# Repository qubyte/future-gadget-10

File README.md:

# FG-10

Design files for the FG-10 custom mechanical keyboard.

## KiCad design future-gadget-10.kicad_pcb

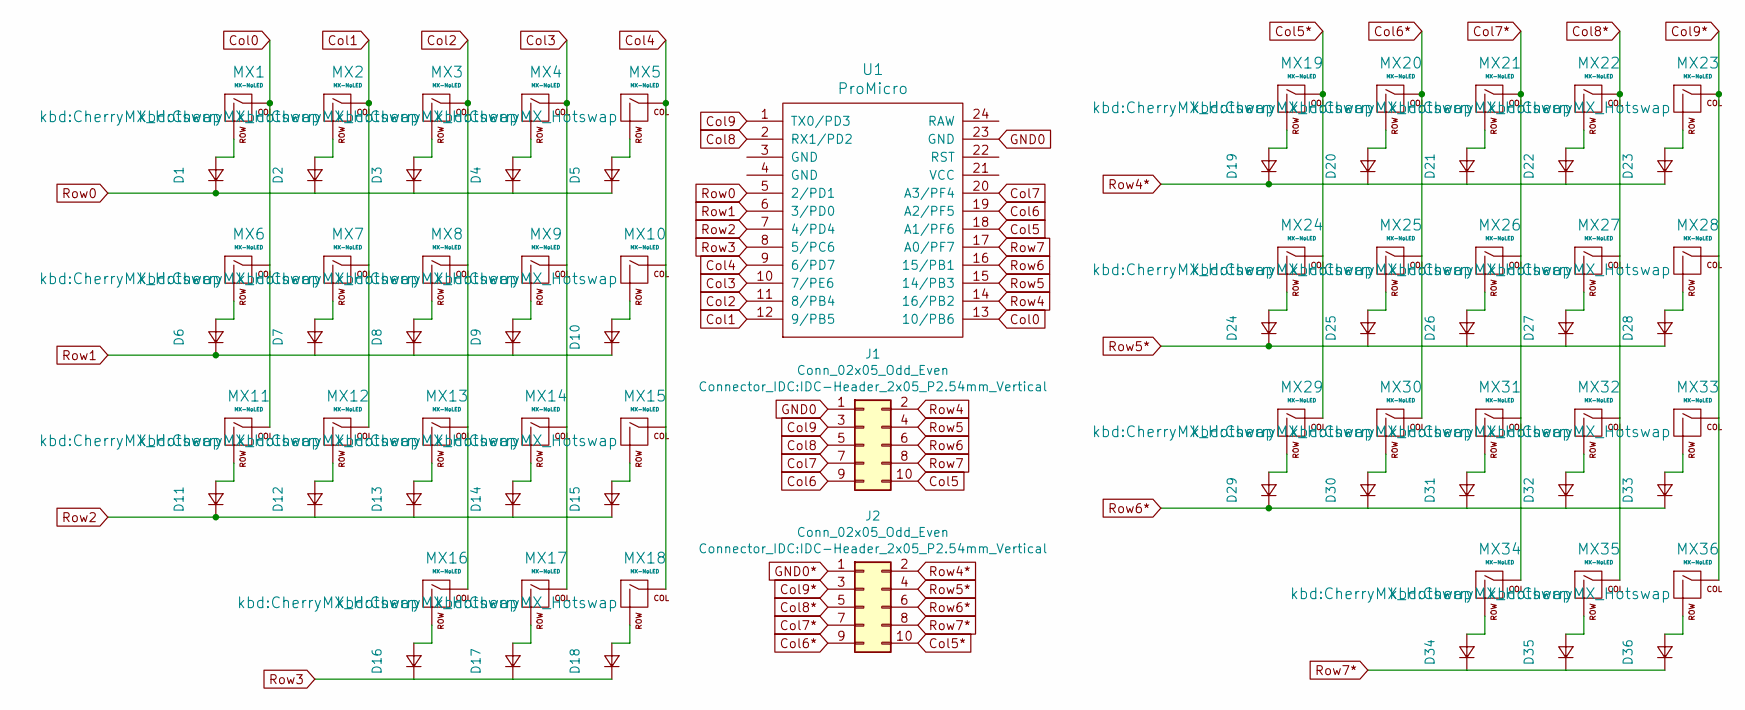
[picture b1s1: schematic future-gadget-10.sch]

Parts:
D1, D2, D3, D4, D5, D6, D7, D8, D9, D10, D11, D12, D13, D14, D15, D16, D17, D18, D19, D20, D21, D22, D23, D24, D25, D26, D27, D28, D29, D30, D31, D32, D33, D34, D35, D36: D_Small; D_SOD-123
J1, J2: Conn_02x05_Odd_Even; IDC-Header_2x05_P2.54mm_Vertical
MX1, MX2, MX3, MX4, MX5, MX6, MX7, MX8, MX9, MX10, MX11, MX12, MX13, MX14, MX15, MX16, MX17, MX18, MX19, MX20, MX21, MX22, MX23, MX24, MX25, MX26, MX27, MX28, MX29, MX30, MX31, MX32, MX33, MX34, MX35, MX36: MX-NoLED; CherryMX_Hotswap
U1: ProMicro; Elite-C

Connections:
Col0: MX1.1 (COL), MX6.1 (COL), MX11.1 (COL), U1.13 (10/PB6)
Col1: MX2.1 (COL), MX7.1 (COL), MX12.1 (COL), U1.12 (9/PB5)
Col2: MX3.1 (COL), MX8.1 (COL), MX13.1 (COL), MX16.1 (COL), U1.11 (8/PB4)
Col3: MX4.1 (COL), MX9.1 (COL), MX14.1 (COL), MX17.1 (COL), U1.10 (7/PE6)
Col4: MX5.1 (COL), MX10.1 (COL), MX15.1 (COL), MX18.1 (COL), U1.9 (6/PD7)
Col5: J1.10, U1.18 (A1/PF6)
Col5*: J2.10, MX19.1 (COL), MX24.1 (COL), MX29.1 (COL)
Col6: J1.9, U1.19 (A2/PF5)
Col6*: J2.9, MX20.1 (COL), MX25.1 (COL), MX30.1 (COL)
Col7: J1.7, U1.20 (A3/PF4)
Col7*: J2.7, MX21.1 (COL), MX26.1 (COL), MX31.1 (COL), MX34.1 (COL)
Col8: J1.5, U1.2 (RX1/PD2)
Col8*: J2.5, MX22.1 (COL), MX27.1 (COL), MX32.1 (COL), MX35.1 (COL)
Col9: J1.3, U1.1 (TX0/PD3)
Col9*: J2.3, MX23.1 (COL), MX28.1 (COL), MX33.1 (COL), MX36.1 (COL)
GND0: J1.1, U1.23 (GND)
GND0*: J2.1
unnamed: D1.2 (A), MX1.2 (ROW)
unnamed: D2.2 (A), MX2.2 (ROW)
unnamed: D3.2 (A), MX3.2 (ROW)
unnamed: D4.2 (A), MX4.2 (ROW)
unnamed: D5.2 (A), MX5.2 (ROW)
unnamed: D6.2 (A), MX6.2 (ROW)
unnamed: D7.2 (A), MX7.2 (ROW)
unnamed: D8.2 (A), MX8.2 (ROW)
unnamed: D9.2 (A), MX9.2 (ROW)
unnamed: D10.2 (A), MX10.2 (ROW)
unnamed: D11.2 (A), MX11.2 (ROW)
unnamed: D12.2 (A), MX12.2 (ROW)
unnamed: D13.2 (A), MX13.2 (ROW)
unnamed: D14.2 (A), MX14.2 (ROW)
unnamed: D15.2 (A), MX15.2 (ROW)
unnamed: D16.2 (A), MX16.2 (ROW)
unnamed: D17.2 (A), MX17.2 (ROW)
unnamed: D18.2 (A), MX18.2 (ROW)
unnamed: D19.2 (A), MX19.2 (ROW)
unnamed: D20.2 (A), MX20.2 (ROW)
unnamed: D21.2 (A), MX21.2 (ROW)
unnamed: D22.2 (A), MX22.2 (ROW)
unnamed: D23.2 (A), MX23.2 (ROW)
unnamed: D24.2 (A), MX24.2 (ROW)
unnamed: D25.2 (A), MX25.2 (ROW)
unnamed: D26.2 (A), MX26.2 (ROW)
unnamed: D27.2 (A), MX27.2 (ROW)
unnamed: D28.2 (A), MX28.2 (ROW)
unnamed: D29.2 (A), MX29.2 (ROW)
unnamed: D30.2 (A), MX30.2 (ROW)
unnamed: D31.2 (A), MX31.2 (ROW)
unnamed: D32.2 (A), MX32.2 (ROW)
unnamed: D33.2 (A), MX33.2 (ROW)
unnamed: D34.2 (A), MX34.2 (ROW)
unnamed: D35.2 (A), MX35.2 (ROW)
unnamed: D36.2 (A), MX36.2 (ROW)
Row0: D1.1 (K), D2.1 (K), D3.1 (K), D4.1 (K), D5.1 (K), U1.5 (2/PD1)
Row1: D6.1 (K), D7.1 (K), D8.1 (K), D9.1 (K), D10.1 (K), U1.6 (3/PD0)
Row2: D11.1 (K), D12.1 (K), D13.1 (K), D14.1 (K), D15.1 (K), U1.7 (4/PD4)
Row3: D16.1 (K), D17.1 (K), D18.1 (K), U1.8 (5/PC6)
Row4: J1.2, U1.14 (16/PB2)
Row4*: D19.1 (K), D20.1 (K), D21.1 (K), D22.1 (K), D23.1 (K), J2.2
Row5: J1.4, U1.15 (14/PB3)
Row5*: D24.1 (K), D25.1 (K), D26.1 (K), D27.1 (K), D28.1 (K), J2.4
Row6: J1.6, U1.16 (15/PB1)
Row6*: D29.1 (K), D30.1 (K), D31.1 (K), D32.1 (K), D33.1 (K), J2.6
Row7: J1.8, U1.17 (A0/PF7)
Row7*: D34.1 (K), D35.1 (K), D36.1 (K), J2.8

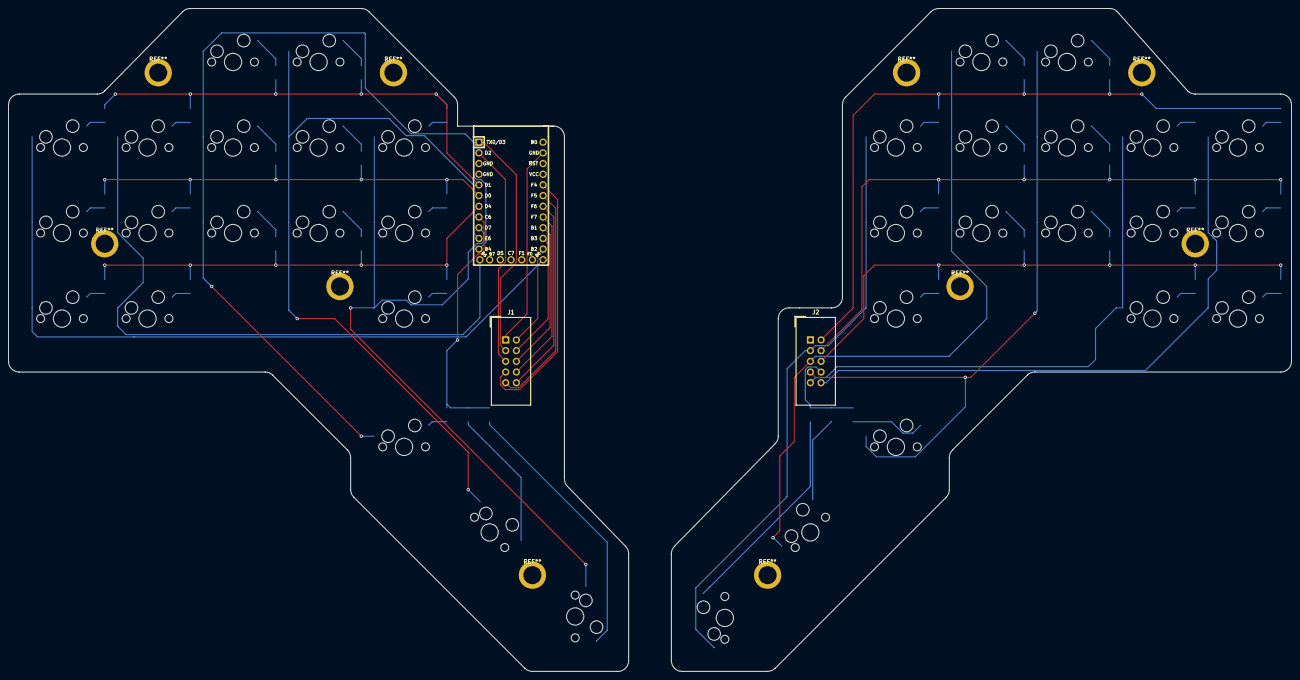
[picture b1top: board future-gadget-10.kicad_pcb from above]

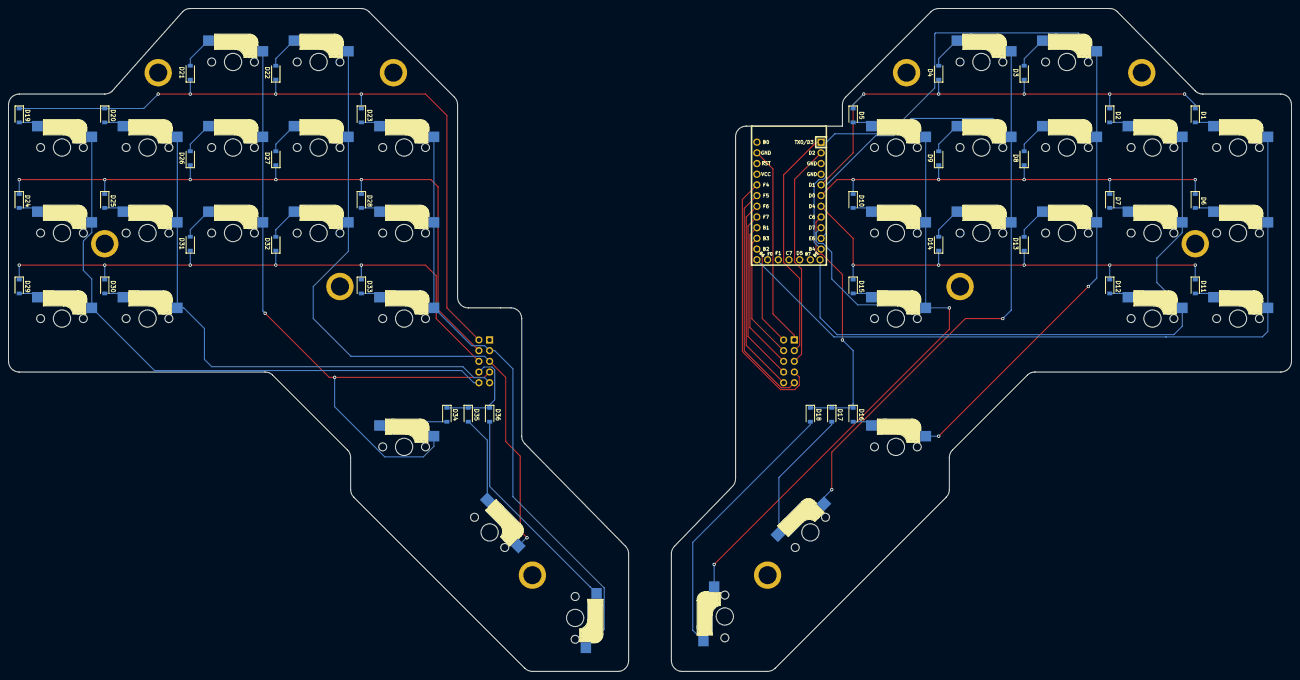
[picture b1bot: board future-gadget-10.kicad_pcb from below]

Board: 2 copper layers, 304.8 x 157.5 mm, 75 parts (36 on the bottom side), 64 nets.

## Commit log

2022-09-07 Initial commit.
2022-09-07 Add license.
2022-09-07 Adds initialized project files.
2022-09-07 Adds submodule for switch footprints.
2022-09-07 Adds symbol tables.
2022-09-10 Snapshot complete left hand.
2022-09-11 Adds right hand, and updates the connector to be vertical to avoid orientation issues.
2022-09-12 A little rerouting and a switch of footprints for the MX hotswaps so they render in 3D.
2022-09-12 Rerouted some tracks to avoid proximity issues.
2022-09-12 A little more rerouting to avoid tracks near solder points.
